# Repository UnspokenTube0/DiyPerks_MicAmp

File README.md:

# DiyPerks_MicAmp
its just a simple pcb for DiyPerks Mic amp.

i had all the parts jut collecting dust thinking that i got a fake That1512, it was just a bad solder joint, was planing in ordering pcbs anyways so i made a quick pcb

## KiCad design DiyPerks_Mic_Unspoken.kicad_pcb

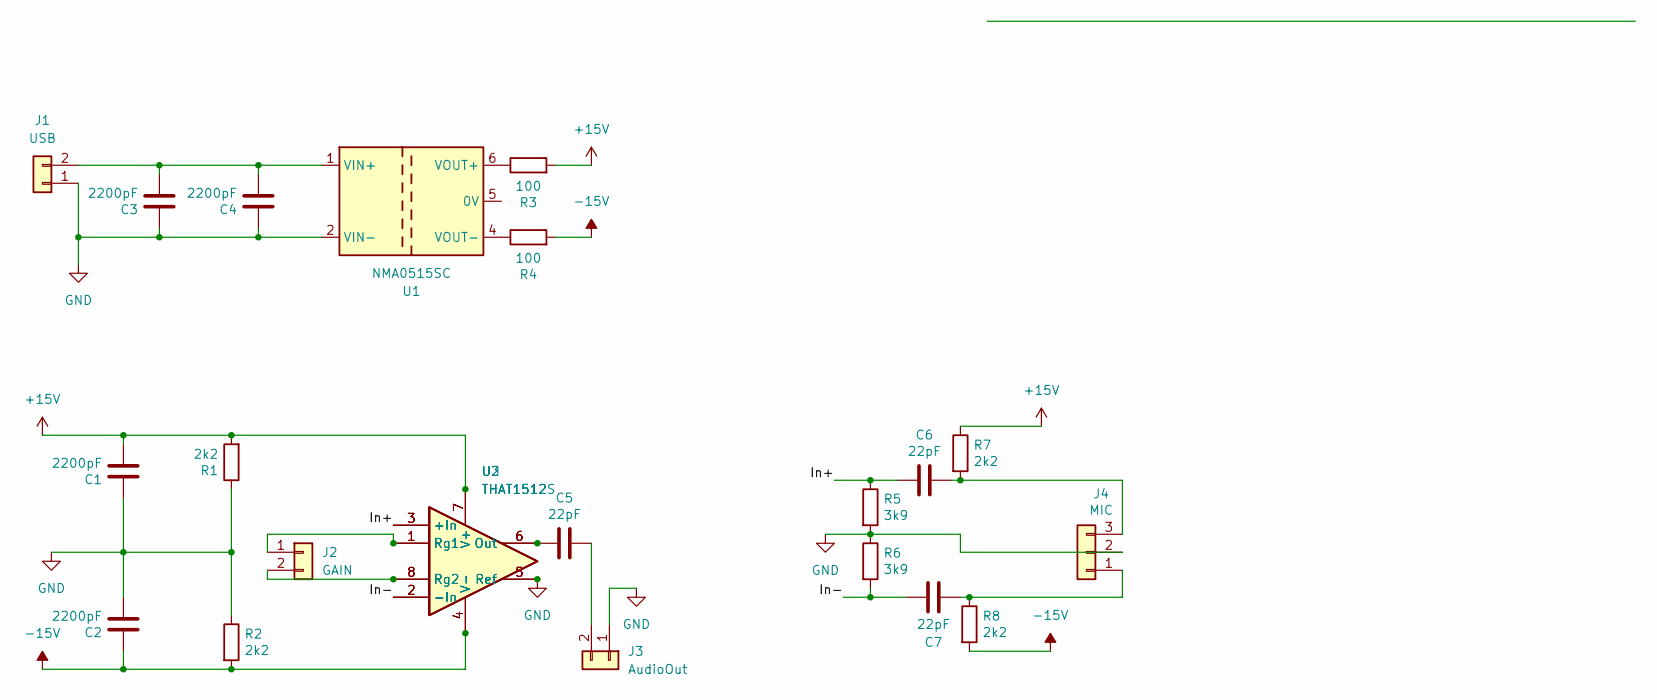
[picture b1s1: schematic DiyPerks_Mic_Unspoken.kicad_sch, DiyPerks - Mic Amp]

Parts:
C1, C2, C3, C4: 2200pF; CP_Radial_D12.5mm_P2.50mm
C5, C6, C7: 22pF; CP_Radial_D7.5mm_P2.50mm
J1: USB; JST_XH_B2B-XH-A_1x02_P2.50mm_Vertical
J2: GAIN; JST_XH_B2B-XH-A_1x02_P2.50mm_Vertical
J3: AudioOut; JST_XH_B2B-XH-A_1x02_P2.50mm_Vertical
J4: MIC; JST_XH_B3B-XH-A_1x03_P2.50mm_Vertical
R1, R2, R7, R8: 2k2; R_Axial_DIN0207_L6.3mm_D2.5mm_P10.16mm_Horizontal
R3, R4: 100; R_Axial_DIN0207_L6.3mm_D2.5mm_P10.16mm_Horizontal
R5, R6: 3k9; R_Axial_DIN0207_L6.3mm_D2.5mm_P10.16mm_Horizontal
U1: NMA0515SC; Converter_DCDC_Murata_NMAxxxxSC_THT
U2: THAT1512S; DIP-8_W8.89mm_SMDSocket_LongPads
U3: THAT1512; DIP-8_W7.62mm_Socket

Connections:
+15V: C1.1, R1.2, R3.2, R7.1, U2.7 (V+), U3.7 (V+)
-15V: C2.2, R2.2, R4.2, R8.2, U2.4 (V-), U3.4 (V-)
/In+: C6.2, R5.1, U2.3 (+In), U3.3 (+In)
/In-: C7.2, R6.2, U2.2 (-In), U3.2 (-In)
GND: C1.2, C2.1, C3.2, C4.2, J1.1, J3.1, J4.2, R1.1, R2.1, R5.2, R6.1, U1.2 (VIN-), U2.5 (Ref), U3.5 (Ref)
unnamed: C3.1, C4.1, J1.2, U1.1 (VIN+)
unnamed: J2.1, U2.1 (Rg1), U3.1 (Rg1)
unnamed: J2.2, U2.8 (Rg2), U3.8 (Rg2)
unnamed: C5.1, J3.2
unnamed: C7.1, J4.1, R8.1
unnamed: C6.1, J4.3, R7.2
unnamed: R3.1, U1.6 (VOUT+)
unnamed: R4.1, U1.4 (VOUT-)
unnamed: C5.2, U2.6 (Out), U3.6 (Out)

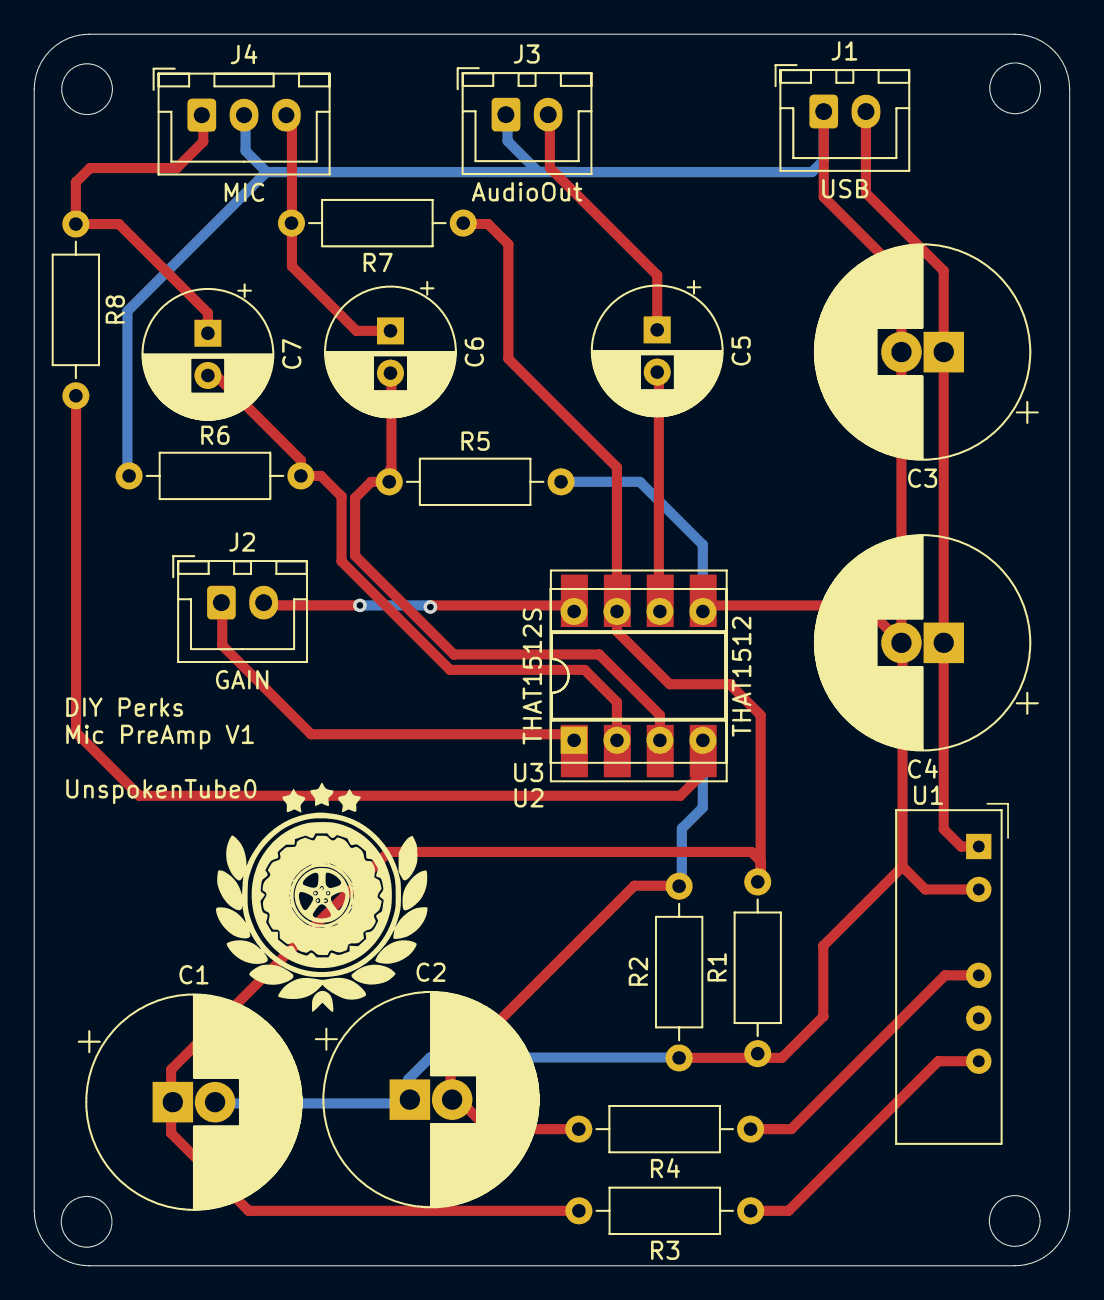
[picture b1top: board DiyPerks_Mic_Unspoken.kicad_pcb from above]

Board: 2 copper layers, 61.2 x 72.8 mm, 22 parts (0 on the bottom side), 14 nets.

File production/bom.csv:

Designator,Footprint,Quantity,Value,LCSC Part #
"_4, _3, _2, ",,4,,
"C1, C2, C3, C4",CP_Radial_D12.5mm_P2.50mm,4,2200pF,
"C5, C6, C7",CP_Radial_D7.5mm_P2.50mm,3,22pF,
J1,JST_XH_B2B-XH-A_1x02_P2.50mm_Vertical,1,USB,
J2,JST_XH_B2B-XH-A_1x02_P2.50mm_Vertical,1,GAIN,
J3,JST_XH_B2B-XH-A_1x02_P2.50mm_Vertical,1,AudioOut,
J4,JST_XH_B3B-XH-A_1x03_P2.50mm_Vertical,1,MIC,
"R1, R2, R7, R8",R_Axial_DIN0207_L6.3mm_D2.5mm_P10.16mm_Horizontal,4,2k2,
"R3, R4",R_Axial_DIN0207_L6.3mm_D2.5mm_P10.16mm_Horizontal,2,100,
"R5, R6",R_Axial_DIN0207_L6.3mm_D2.5mm_P10.16mm_Horizontal,2,3k9,
U1,Converter_DCDC_Murata_NMAxxxxSC_THT,1,NMA0515SC,
U2,DIP-8_W8.89mm_SMDSocket_LongPads,1,THAT1512S,
U3,DIP-8_W7.62mm_Socket,1,THAT1512,
